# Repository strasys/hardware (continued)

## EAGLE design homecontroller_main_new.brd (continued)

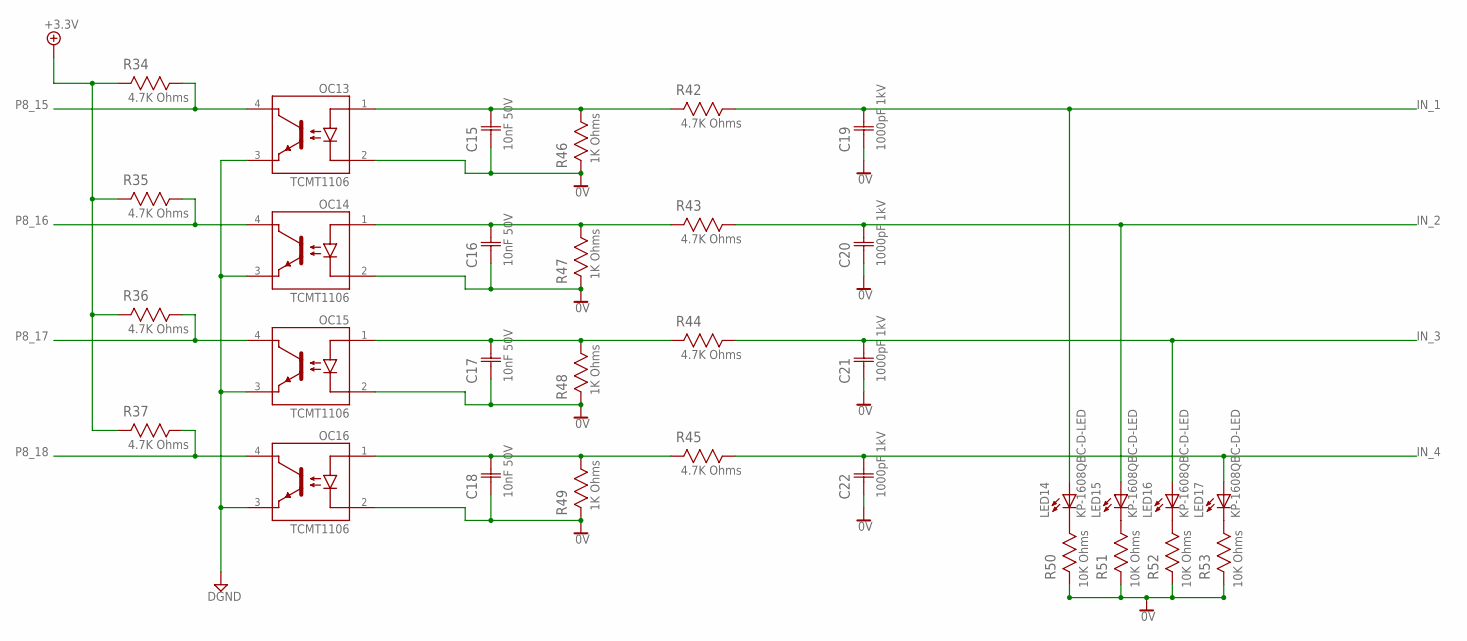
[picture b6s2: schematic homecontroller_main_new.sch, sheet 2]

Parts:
C15, C16, C17, C18: 10nF 50V; CAPC1608X85N
C19, C20, C21, C22: 1000pF 1kV; CAPC3216X88N
LED14, LED15, LED16, LED17: KP-1608QBC-D-LED; KP-1608QBCD-D-LED; MPN KP-1608QBC-D
OC13, OC14, OC15, OC16: TCMT1106; SOP-4
R34, R35, R36, R37, R42, R43, R44, R45: 4.7K Ohms; RESC1608X60N
R46, R47, R48, R49: 1K Ohms; RESC1608X60N
R50, R51, R52, R53: 10K Ohms; RESC1608X60N

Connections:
0V: C15.1 (C1), C16.1 (C1), C17.1 (C1), C18.1 (C1), C19.1 (C1), C20.1 (C1), C21.1 (C1), C22.1 (C1), OC13.2, OC14.2, OC15.2, OC16.2, R46.2, R47.2, R48.2, R49.2, R50.2, R51.2, R52.2, R53.2; also elsewhere on the board
+3.3V: R34.2, R35.2, R36.2, R37.2; also elsewhere on the board
DGND: OC13.3, OC14.3, OC15.3, OC16.3; also elsewhere on the board
IN_1: C19.2 (C2), LED14.1, R42.1; also elsewhere on the board
IN_2: C20.2 (C2), LED15.1, R43.1; also elsewhere on the board
IN_3: C21.2 (C2), LED16.1, R44.1; also elsewhere on the board
IN_4: C22.2 (C2), LED17.1, R45.1; also elsewhere on the board
unnamed: LED14.2, R50.1
unnamed: LED15.2, R51.1
unnamed: LED16.2, R52.1
unnamed: LED17.2, R53.1
unnamed: C15.2 (C2), OC13.1, R42.2, R46.1
unnamed: C16.2 (C2), OC14.1, R43.2, R47.1
unnamed: C17.2 (C2), OC15.1, R44.2, R48.1
unnamed: C18.2 (C2), OC16.1, R45.2, R49.1
P8_15: OC13.4, R34.1; also elsewhere on the board
P8_16: OC14.4, R35.1; also elsewhere on the board
P8_17: OC15.4, R36.1; also elsewhere on the board
P8_18: OC16.4, R37.1; also elsewhere on the board

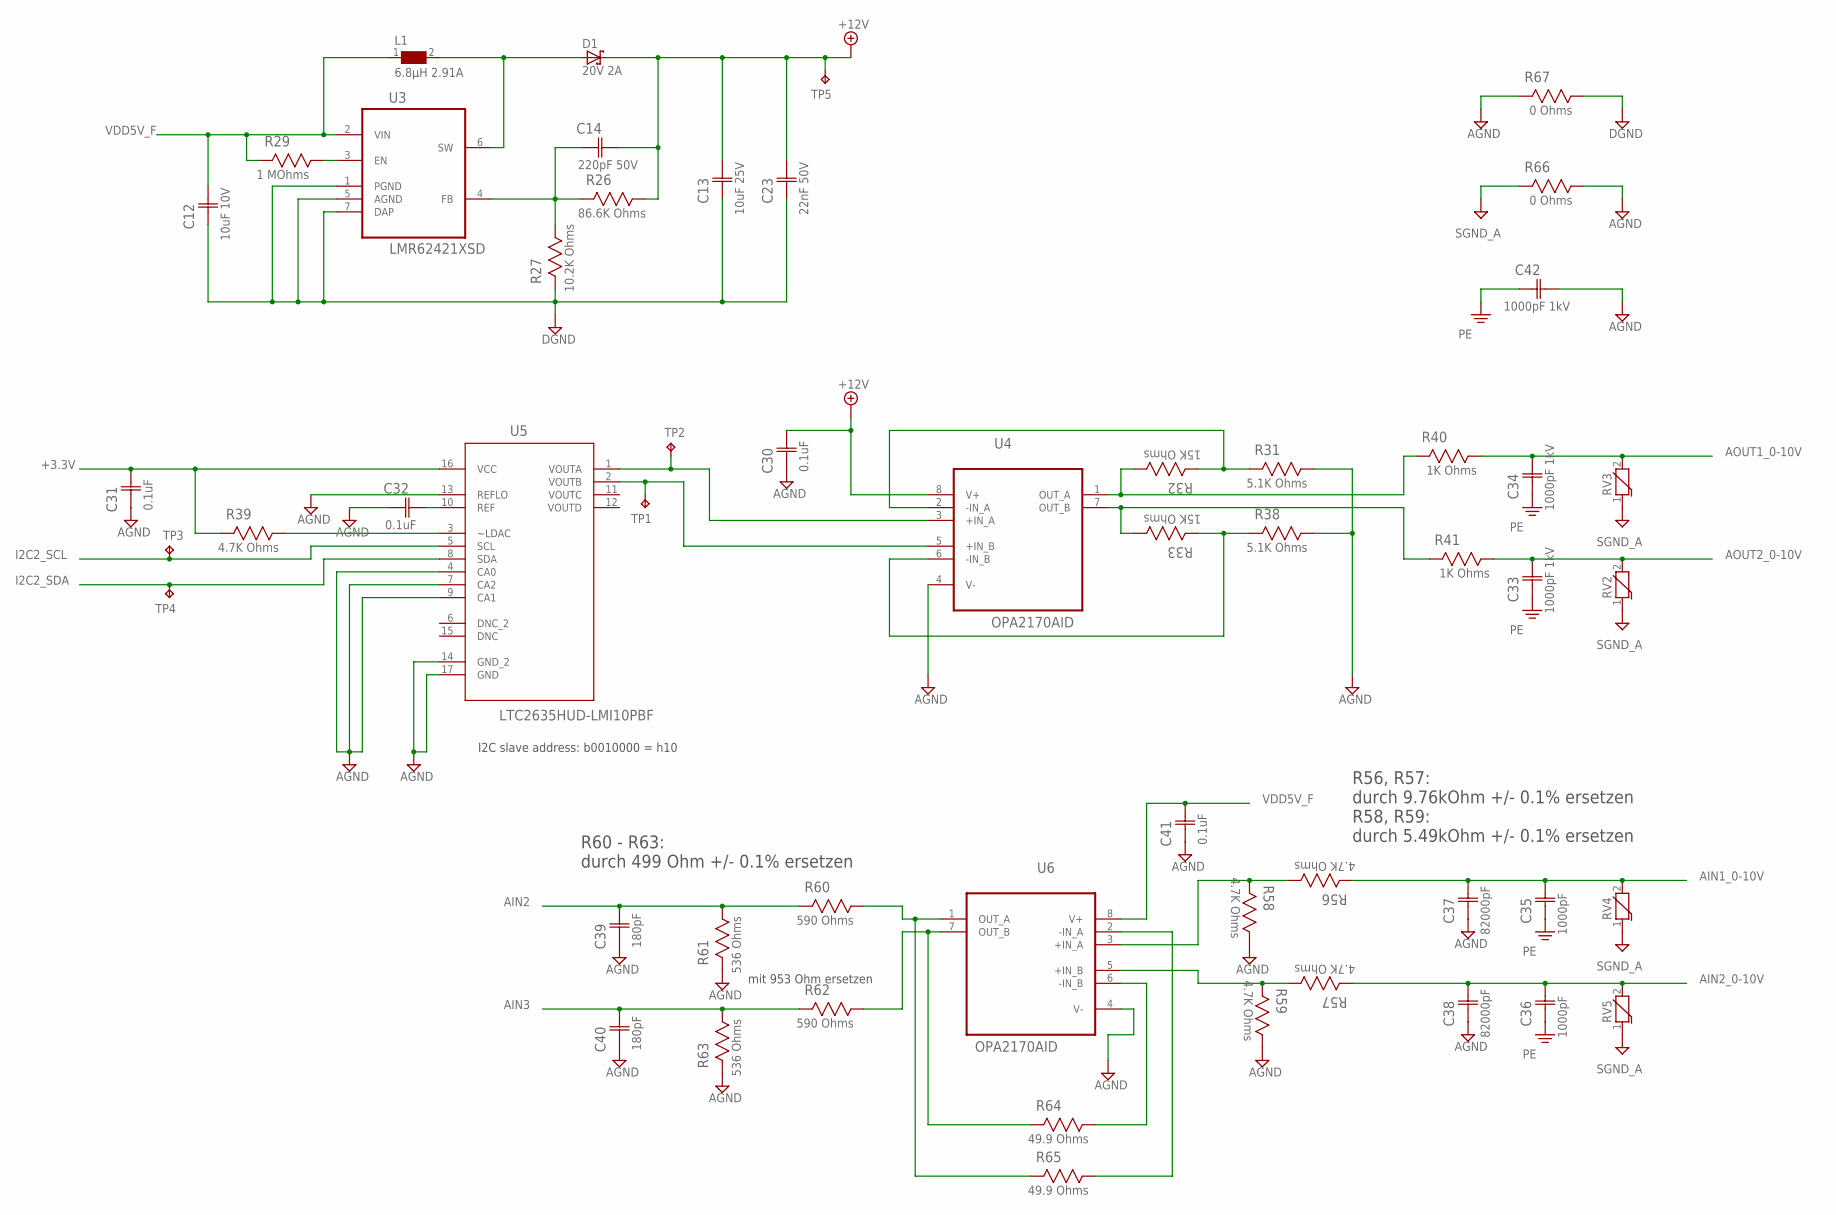
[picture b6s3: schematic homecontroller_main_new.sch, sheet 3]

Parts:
C12: 10uF 10V; CAPC2013X140N
C13: 10uF 25V; CAPC3216X180N
C14: 220pF 50V; CAPC1608X85N
C23: 22nF 50V; CAPC1608X85N
C30, C31, C32, C41: 0.1uF; CAPC1608X85N; MPN C0603C104K5RACTU
C33, C34, C42: 1000pF 1kV; CAPC3216X88N
C35, C36: 1000pF; CAPC3216X88N
C37, C38: 82000pF; CAPC1608X85N
C39, C40: 180pF; CAPC1608X85N
D1: 20V 2A; SMB
L1: 6.8µH 2.91A; WE-PD_7332/7345_PLASTIC_BASE
R26: 86.6K Ohms; RESC1608X60N
R27: 10.2K Ohms; RESC1608X60N
R29: 1 MOhms; RESC1608X60N
R31, R38: 5.1K Ohms; RESC1608X60N
R32, R33: 15K Ohms; RESC1608X60N
R39, R56, R57, R58, R59: 4.7K Ohms; RESC1608X60N
R40, R41: 1K Ohms; RESC1608X60N
R60, R62: 590 Ohms; RESC1608X60N
R61, R63: 536 Ohms; RESC1608X60N
R64, R65: 49.9 Ohms; RESC1608X60N
R66, R67: 0 Ohms; RESC3216X71N
RV2, RV3, RV4, RV5: WE-VS-82536140_0603; WESURGE_0603
TP1, TP2, TP3, TP4, TP5: TPB1,27; B1,27
U3: LMR62421XSD; DFN300X300X80-7N
U4, U6: OPA2170AID; SOIC127P600X175-8N
U5: LTC2635HUD-LMI10PBF; QFN50P300X300X80-17N

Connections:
+3.3V: C31.2 (C2), R39.2, U5.16 (VCC); also elsewhere on the board
+12V: C13.2 (C2), C14.2 (C2), C23.2 (C2), C30.2 (C2), D1.C, R26.1, TP5.TP, U4.8 (V+)
AGND: C30.1 (C1), C31.1 (C1), C32.1 (C1), C37.1 (C1), C38.1 (C1), C39.1 (C1), C40.1 (C1), C41.1 (C1), C42.2 (C2), R31.1, R38.1, R58.1, R59.1, R61.2, R63.2, R66.1, R67.2, U4.4 (V-), U5.4 (CA0), U5.7 (CA2), U5.9 (CA1), U5.13 (REFLO), U5.14 (GND_2), U5.17 (GND), U6.4 (V-); also elsewhere on the board
AIN1_0-10V: C35.2 (C2), C37.2 (C2), R56.2, RV4.2; also elsewhere on the board
AIN2: C39.2 (C2), R60.2, R61.1; also elsewhere on the board
AIN2_0-10V: C36.2 (C2), C38.2 (C2), R57.2, RV5.2; also elsewhere on the board
AIN3: C40.2 (C2), R62.2, R63.1; also elsewhere on the board
AOUT1_0-10V: C34.2 (C2), R40.1, RV3.2; also elsewhere on the board
AOUT2_0-10V: C33.2 (C2), R41.1, RV2.2; also elsewhere on the board
DGND: C12.1 (C1), C13.1 (C1), C23.1 (C1), R27.2, R67.1, U3.1 (PGND), U3.5 (AGND), U3.7 (DAP); also elsewhere on the board
FB_LMR62: C14.1 (C1), R26.2, R27.1, U3.4 (FB)
I2C2_SCL: TP3.TP, U5.5 (SCL); also elsewhere on the board
I2C2_SDA: TP4.TP, U5.8 (SDA); also elsewhere on the board
LDAC: R39.1, U5.3 (~LDAC)
unnamed: R56.1, R58.2, U6.3 (+IN_A)
unnamed: R29.1, U3.3 (EN)
unnamed: R57.1, R59.2, U6.5 (+IN_B)
unnamed: C32.2 (C2), U5.10 (REF)
OPA21_-IN_A: R31.2, R32.2, U4.2 (-IN_A)
OPA21_-IN_B: R33.2, R38.2, U4.6 (-IN_B)
OPA21_AOUTB: R33.1, R41.2, U4.7 (OUT_B)
OPA21_OUT_A: R32.1, R40.2, U4.1 (OUT_A)
OPA2170_-IN_A_2: R65.1, U6.2 (-IN_A)
OPA2170_-IN_B_2: R64.1, U6.6 (-IN_B)
OPA2170_OUT_A_2: R60.1, R65.2, U6.1 (OUT_A)
OPA2170_OUT_B_2: R62.1, R64.2, U6.7 (OUT_B)
PE: C33.1 (C1), C34.1 (C1), C35.1 (C1), C36.1 (C1), C42.1 (C1); also elsewhere on the board
SGND_A: R66.2, RV2.1, RV3.1, RV4.1, RV5.1; also elsewhere on the board
SW_LMR62: D1.A, L1.2, U3.6 (SW)
VDD5V_F: C12.2 (C2), C41.2 (C2), L1.1, R29.2, U3.2 (VIN), U6.8 (V+); also elsewhere on the board
VOUTA: TP2.TP, U4.3 (+IN_A), U5.1 (VOUTA)
VOUTB: TP1.TP, U4.5 (+IN_B), U5.2 (VOUTB)

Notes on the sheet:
I2C slave address: b0010000 = h10
R60 - R63: durch 499 Ohm +/- 0.1% ersetzen
mit 953 Ohm ersetzen
R56, R57: durch 9.76kOhm +/- 0.1% ersetzen R58, R59: durch 5.49kOhm +/- 0.1% ersetzen

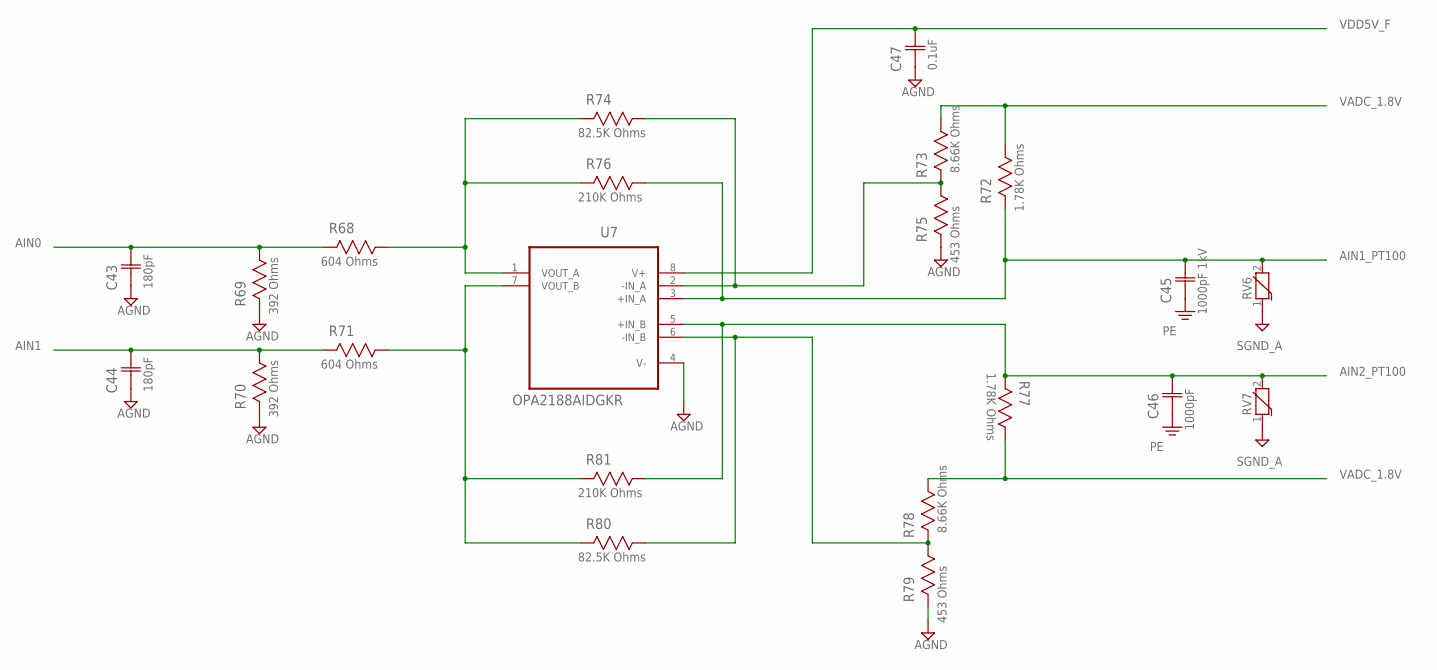
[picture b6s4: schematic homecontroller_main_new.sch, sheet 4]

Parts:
C43, C44: 180pF; CAPC1608X85N
C45: 1000pF 1kV; CAPC3216X88N
C46: 1000pF; CAPC3216X88N
C47: 0.1uF; CAPC1608X85N; MPN C0603C104K5RACTU
R68, R71: 604 Ohms; RESC1608X60N
R69, R70: 392 Ohms; RESC1608X60N
R72, R77: 1.78K Ohms; RESC1608X60N
R73, R78: 8.66K Ohms; RESC1608X60N
R74, R80: 82.5K Ohms; RESC1608X60N
R75, R79: 453 Ohms; RESC1608X60N
R76, R81: 210K Ohms; RESC1608X60N
RV6, RV7: WE-VS-82536140_0603; WESURGE_0603
U7: OPA2188AIDGKR; SOP65P490X110-8N

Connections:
AGND: C43.1 (C1), C44.1 (C1), C47.1 (C1), R69.2, R70.2, R75.2, R79.2, U7.4 (V-); also elsewhere on the board
AIN0: C43.2 (C2), R68.2, R69.1; also elsewhere on the board
AIN1: C44.2 (C2), R70.1, R71.2; also elsewhere on the board
AIN1_PT100: C45.2 (C2), R72.2, R76.1, RV6.2, U7.3 (+IN_A); also elsewhere on the board
AIN2_PT100: C46.2 (C2), R77.2, R81.1, RV7.2, U7.5 (+IN_B); also elsewhere on the board
OPA2188_-IN_A: R73.2, R74.1, R75.1, U7.2 (-IN_A)
OPA2188_-IN_B: R78.2, R79.1, R80.1, U7.6 (-IN_B)
OPA2188_VOUT_A: R68.1, R74.2, R76.2, U7.1 (VOUT_A)
OPA2188_VOUT_B: R71.1, R80.2, R81.2, U7.7 (VOUT_B)
PE: C45.1 (C1), C46.1 (C1); also elsewhere on the board
SGND_A: RV6.1, RV7.1; also elsewhere on the board
VADC_1.8V: R72.1, R73.1, R77.1, R78.1; also elsewhere on the board
VDD5V_F: C47.2 (C2), U7.8 (V+); also elsewhere on the board

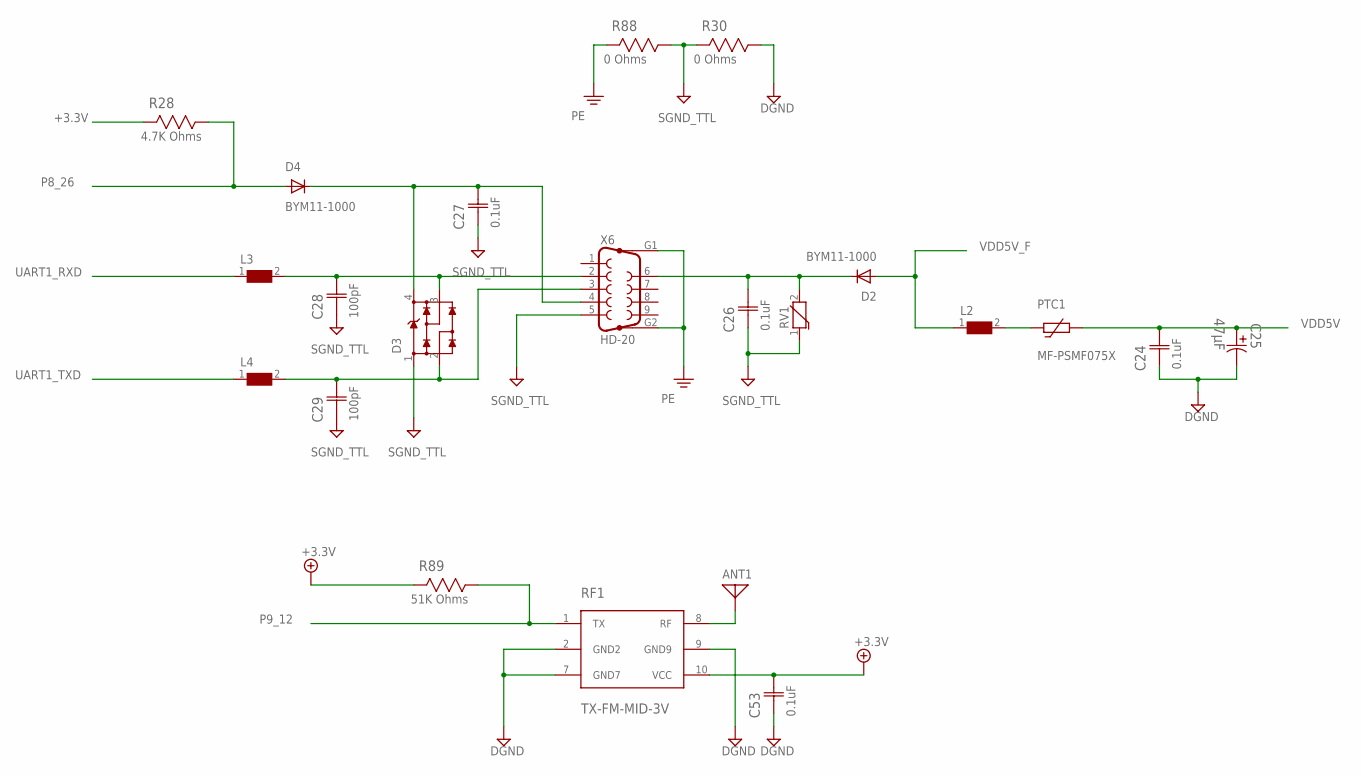
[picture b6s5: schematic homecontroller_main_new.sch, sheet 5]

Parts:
ANT1: ANTENNA; PAD-01
C24, C26, C27, C53: 0.1uF; CAPC1608X85N; MPN C0603C104K5RACTU
C25: 47µF; CAPAE830X650N; MPN EEEFK1H470P
C28, C29: 100pF; CAPC1608X85N
D2, D4: BYM11-1000; DO-213AB
D3: WE-TVS_8240136; WE-TVS_SOT143-4L
L2: WE-CBF-74279218_1206; 1206
L3, L4: WE-CBF-74279263_0603; 0603
PTC1: MF-PSMF075X; MF-PSMF
R28: 4.7K Ohms; RESC1608X60N
R30, R88: 0 Ohms; RESC3216X71N
R89: 51K Ohms; RESC1608X60N
RF1: TX-FM-MID-3V; TX_SAW_MID
RV1: WE-VS-82536040_0603; WESURGE_0603; MPN 82536140
X6: HD-20; SUB-D_HD-20; MPN 1734354-1.

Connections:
+3.3V: C53.2 (C2), R28.2, R89.2, RF1.10 (VCC); also elsewhere on the board
+5V: C26.2 (C2), D2.C, RV1.2, X6.6
DGND: C24.1 (C1), C25.2, C53.1 (C1), R30.1, RF1.2 (GND2), RF1.7 (GND7), RF1.9 (GND9); also elsewhere on the board
unnamed: ANT1.1, RF1.8 (RF)
unnamed: L2.2, PTC1.P$1
P8_26: D4.A, R28.1; also elsewhere on the board
P9_12: R89.1, RF1.1 (TX); also elsewhere on the board
PE: R88.2, X6.G1, X6.G2; also elsewhere on the board
RESET: C27.2 (C2), D3.4 (VDD), D4.C, X6.4
SGND_TTL: C26.1 (C1), C27.1 (C1), C28.1 (C1), C29.1 (C1), D3.1 (GND), R30.2, R88.1, RV1.1, X6.5
UART1_RXD: L3.1; also elsewhere on the board
UART1_RXD_S: C28.2 (C2), D3.3 (2), L3.2, X6.2
UART1_TXD: L4.1; also elsewhere on the board
UART1_TXD_S: C29.2 (C2), D3.2 (1), L4.2, X6.3
VDD5V: C24.2 (C2), C25.1, PTC1.P$2; also elsewhere on the board
VDD5V_F: D2.A, L2.1; also elsewhere on the board

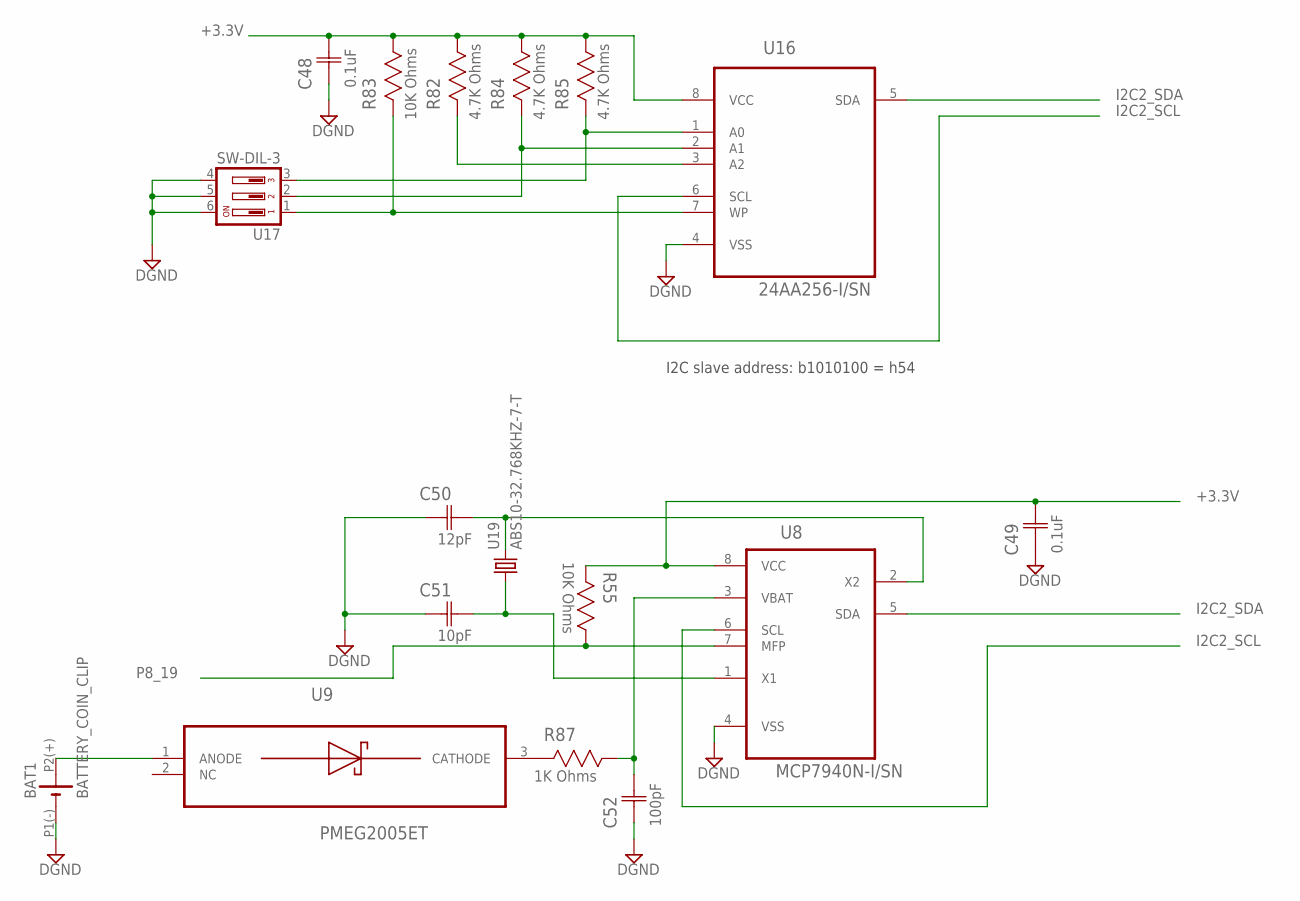
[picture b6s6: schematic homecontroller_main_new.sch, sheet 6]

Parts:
BAT1: BATTERY_COIN_CLIP; BAT_HOLDER_16MM
C48, C49: 0.1uF; CAPC1608X85N; MPN C0603C104K5RACTU
C50: 12pF; CAPC1608X85N
C51: 10pF; CAPC1608X85N
C52: 100pF; CAPC1608X85N
R55, R83: 10K Ohms; RESC1608X60N
R82, R84, R85: 4.7K Ohms; RESC1608X60N
R87: 1K Ohms; RESC1608X60N
U8: MCP7940N-I/SN; SOIC127P600X175-8N; MPN MCP7940N-I/SN
U9: PMEG2005ET; SOT95P280X145-5N
U16: 24AA256-I/SN; SOIC127P600X175-8N
U17: SW-DIL-3; DS-03
U19: ABS10-32.768KHZ-7-T; ABS-10

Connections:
24AA_A0: R85.2, U16.1 (A0), U17.3
24AA_A1: R84.2, U16.2 (A1), U17.2
24AA_WP: R83.2, U16.7 (WP), U17.1
+3.3V: C48.2 (C2), C49.2 (C2), R55.2, R82.1, R83.1, R84.1, R85.1, U8.8 (VCC), U16.8 (VCC); also elsewhere on the board
DGND: BAT1.P1(-) (-), C48.1 (C1), C49.1 (C1), C50.1 (C1), C51.1 (C1), C52.1 (C1), U8.4 (VSS), U16.4 (VSS), U17.4, U17.5, U17.6; also elsewhere on the board
I2C2_SCL: U8.6 (SCL), U16.6 (SCL); also elsewhere on the board
I2C2_SDA: U8.5 (SDA), U16.5 (SDA); also elsewhere on the board
unnamed: R82.2, U16.3 (A2)
unnamed: BAT1.P2(+) (+), U9.1 (ANODE)
unnamed: R87.2, U9.3 (CATHODE)
unnamed: C52.2 (C2), R87.1, U8.3 (VBAT)
unnamed: C50.2 (C2), U8.2 (X2), U19.P$2 (2)
unnamed: C51.2 (C2), U8.1 (X1), U19.P$1 (1)
P8_19: R55.1, U8.7 (MFP); also elsewhere on the board

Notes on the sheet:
I2C slave address: b1010100 = h54

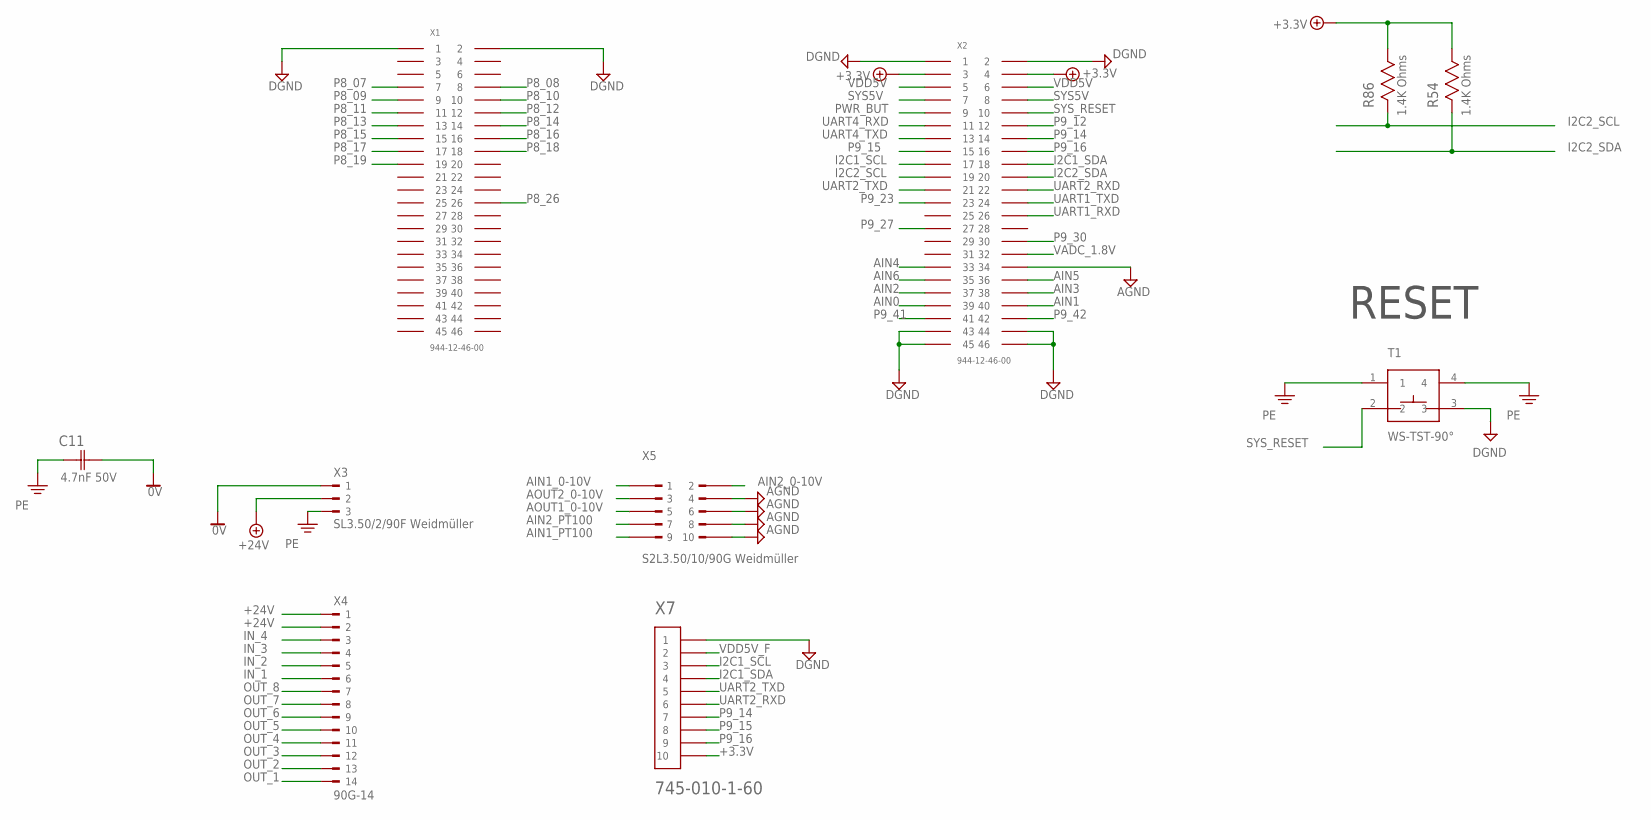
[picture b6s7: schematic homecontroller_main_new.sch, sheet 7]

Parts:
C11: 4.7nF 50V; CAPC1608X85N
R54, R86: 1.4K Ohms; RESC1608X60N
T1: WS-TST-90°
X1, X2: 944-12-46-00; 2,54_STIFTLEIST_2X23
X3: SL3.50/2/90F Weidmüller; 90F-3
X4: 90G-14
X5: S2L3.50/10/90G Weidmüller; S2L-90G-10
X7: 745-010-1-60; 2MM-1-REIH-10

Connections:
0V: C11.2 (C2), X3.1; also elsewhere on the board
+3.3V: R54.1, R86.1, X2.P3 (3), X2.P4 (4), X7.10; also elsewhere on the board
+24V: X3.2, X4.1, X4.2; also elsewhere on the board
AGND: X2.P34 (34), X5.4, X5.6, X5.8, X5.10; also elsewhere on the board
AIN0: X2.P39 (39); also elsewhere on the board
AIN1: X2.P40 (40); also elsewhere on the board
AIN1_0-10V: X5.1; also elsewhere on the board
AIN1_PT100: X5.9; also elsewhere on the board
AIN2: X2.P37 (37); also elsewhere on the board
AIN2_0-10V: X5.2; also elsewhere on the board
AIN2_PT100: X5.7; also elsewhere on the board
AIN3: X2.P38 (38); also elsewhere on the board
AIN4: X2.P33 (33)
AIN5: X2.P36 (36)
AIN6: X2.P35 (35)
AOUT1_0-10V: X5.5; also elsewhere on the board
AOUT2_0-10V: X5.3; also elsewhere on the board
DGND: T1.3, X1.P1 (1), X1.P2 (2), X2.P1 (1), X2.P2 (2), X2.P43 (43), X2.P44 (44), X2.P45 (45), X2.P46 (46), X7.1; also elsewhere on the board
I2C1_SCL: X2.P17 (17), X7.3
I2C1_SDA: X2.P18 (18), X7.4
I2C2_SCL: R86.2, X2.P19 (19); also elsewhere on the board
I2C2_SDA: R54.2, X2.P20 (20); also elsewhere on the board
IN_1: X4.6; also elsewhere on the board
IN_2: X4.5; also elsewhere on the board
IN_3: X4.4; also elsewhere on the board
IN_4: X4.3; also elsewhere on the board
OUT_1: X4.14; also elsewhere on the board
OUT_2: X4.13; also elsewhere on the board
OUT_3: X4.12; also elsewhere on the board
OUT_4: X4.11; also elsewhere on the board
OUT_5: X4.10; also elsewhere on the board
OUT_6: X4.9; also elsewhere on the board
OUT_7: X4.8; also elsewhere on the board
OUT_8: X4.7; also elsewhere on the board
P8_07: X1.P7 (7); also elsewhere on the board
P8_08: X1.P8 (8); also elsewhere on the board
P8_09: X1.P9 (9); also elsewhere on the board
P8_10: X1.P10 (10); also elsewhere on the board
P8_11: X1.P11 (11); also elsewhere on the board
P8_12: X1.P12 (12); also elsewhere on the board
P8_13: X1.P13 (13); also elsewhere on the board
P8_14: X1.P14 (14); also elsewhere on the board
P8_15: X1.P15 (15); also elsewhere on the board
P8_16: X1.P16 (16); also elsewhere on the board
P8_17: X1.P17 (17); also elsewhere on the board
P8_18: X1.P18 (18); also elsewhere on the board
P8_19: X1.P19 (19); also elsewhere on the board
P8_26: X1.P26 (26); also elsewhere on the board
P9_12: X2.P12 (12); also elsewhere on the board
P9_14: X2.P14 (14), X7.7
P9_15: X2.P15 (15), X7.8
P9_16: X2.P16 (16), X7.9
P9_23: X2.P23 (23)
P9_27: X2.P27 (27)
P9_30: X2.P30 (30)
P9_41: X2.P41 (41)
P9_42: X2.P42 (42)
PE: C11.1 (C1), T1.1, T1.4, X3.3; also elsewhere on the board
PWR_BUT: X2.P9 (9)
SYS5V: X2.P7 (7), X2.P8 (8)
SYS_RESET: T1.2, X2.P10 (10)
UART1_RXD: X2.P26 (26); also elsewhere on the board
UART1_TXD: X2.P24 (24); also elsewhere on the board
UART2_RXD: X2.P22 (22), X7.6
UART2_TXD: X2.P21 (21), X7.5
UART4_RXD: X2.P11 (11)
UART4_TXD: X2.P13 (13)
VADC_1.8V: X2.P32 (32); also elsewhere on the board
VDD5V: X2.P5 (5), X2.P6 (6); also elsewhere on the board
VDD5V_F: X7.2; also elsewhere on the board

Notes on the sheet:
RESET

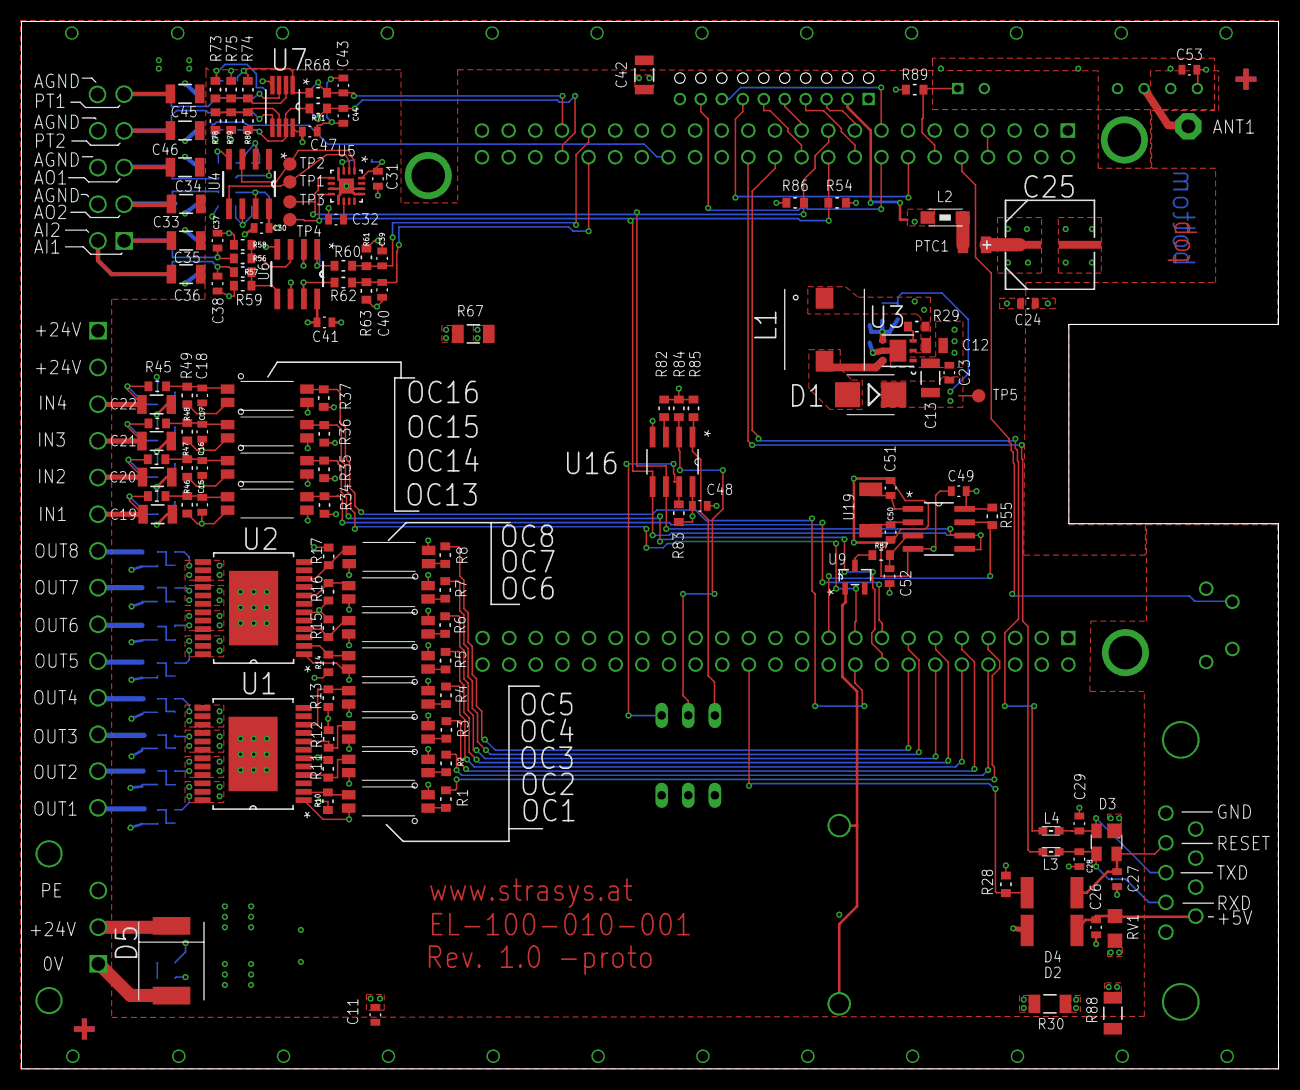
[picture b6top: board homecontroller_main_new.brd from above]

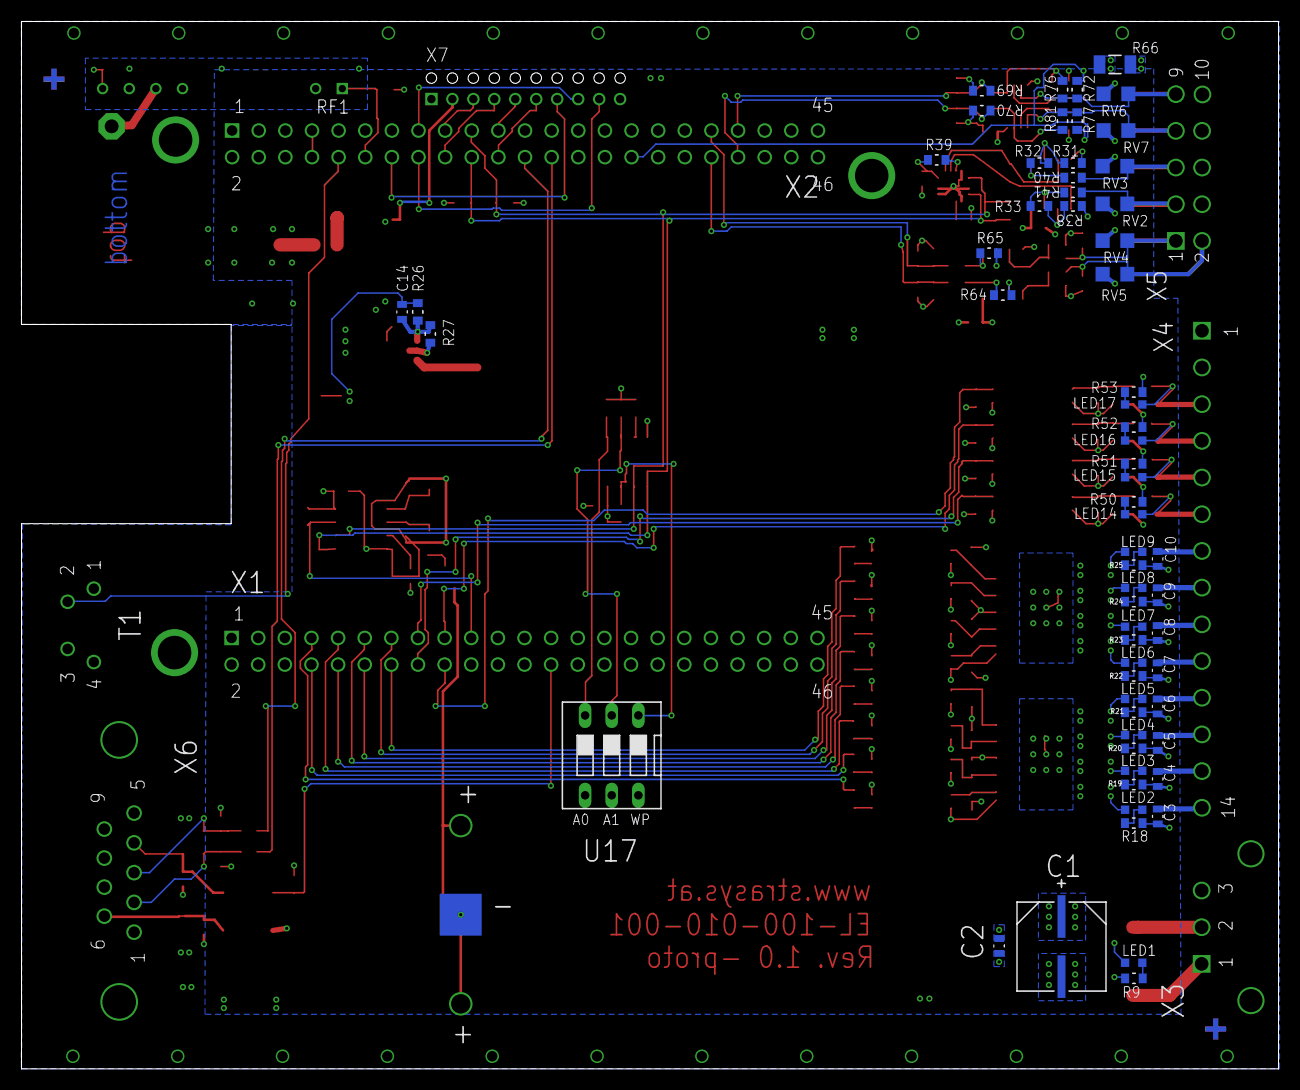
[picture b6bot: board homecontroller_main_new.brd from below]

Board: 4 copper layers, 119.9 x 99.9 mm, 217 parts (74 on the bottom side), 131 nets.

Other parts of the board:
DRILEGEND: DRILEGEND
U$1, U$3, U$16, U$17: PASSER_SMD4

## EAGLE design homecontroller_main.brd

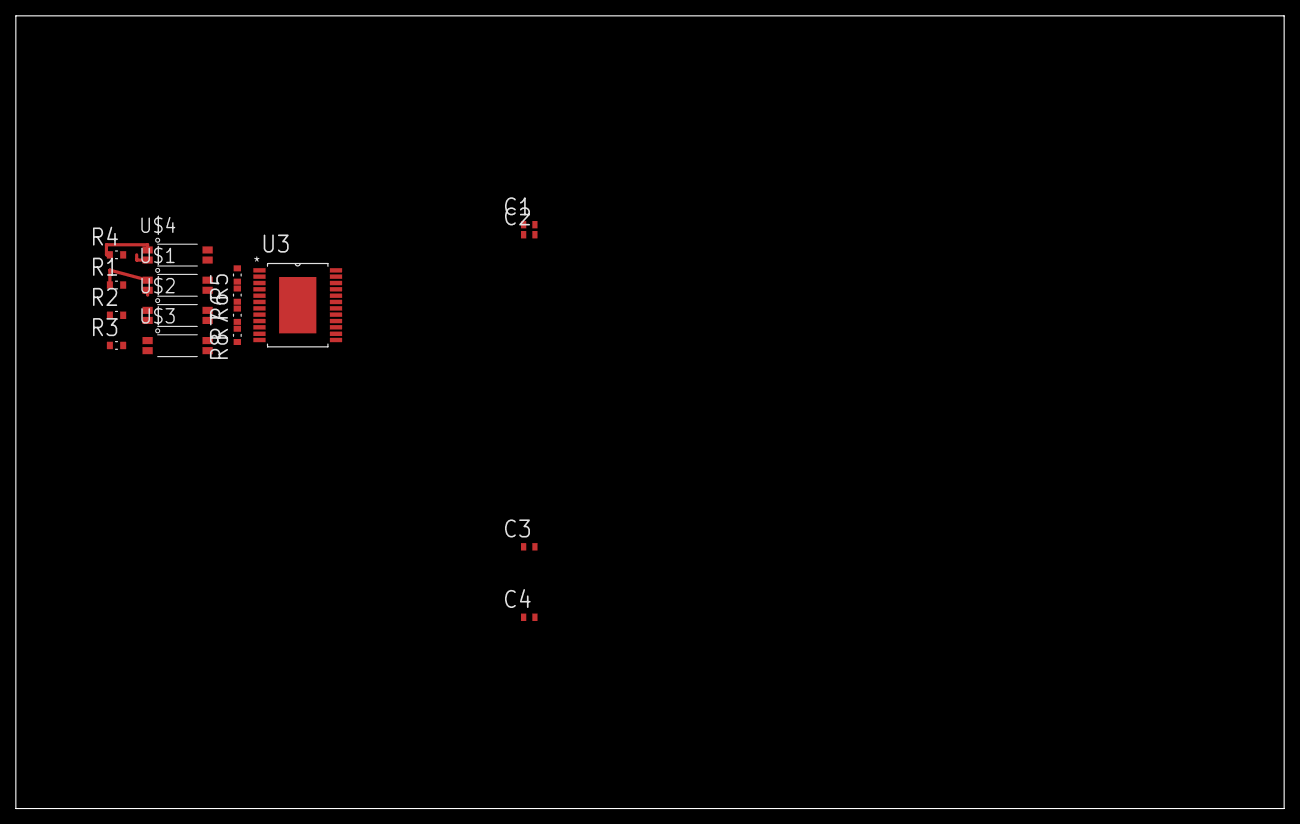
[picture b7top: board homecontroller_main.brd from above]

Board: 2 copper layers, 160.0 x 100.0 mm, 17 parts (0 on the bottom side), 15 nets.

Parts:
C1, C2, C3, C4: 10nF 50V; CAPC1608X85N
R1, R2, R3, R4: 1K Ohms; RESC1608X60N
R5, R6, R7, R8: 47K Ohms; RESC1608X60N
U3: VNI4140K; SOP80P1030X247-25N
U$1, U$2, U$3, U$4: TCMT1106; SOP-4

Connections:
0V: C1.1, C2.1, C3.1, C4.1, R5.2, R6.2, R7.2, R8.2, U3.6
+24V: U3.1, U3.25, U$1.4, U$2.4, U$3.4, U$4.4
DGND: U$1.2, U$2.2, U$3.2
unnamed: R1.1, U$1.1
unnamed: R2.1, U$2.1
unnamed: R3.1, U$3.1
unnamed: R4.1, U$4.1
unnamed: R5.1, U3.2, U$1.3
unnamed: R6.1, U3.4, U$2.3
unnamed: R7.1, U3.8, U$3.3
unnamed: R8.1, U3.10, U$4.3
unnamed: C1.2, U3.22, U3.23, U3.24
OUT_2: C2.2, U3.19, U3.20, U3.21
OUT_3: C3.2, U3.16, U3.17, U3.18
OUT_4: C4.2, U3.13, U3.14, U3.15
